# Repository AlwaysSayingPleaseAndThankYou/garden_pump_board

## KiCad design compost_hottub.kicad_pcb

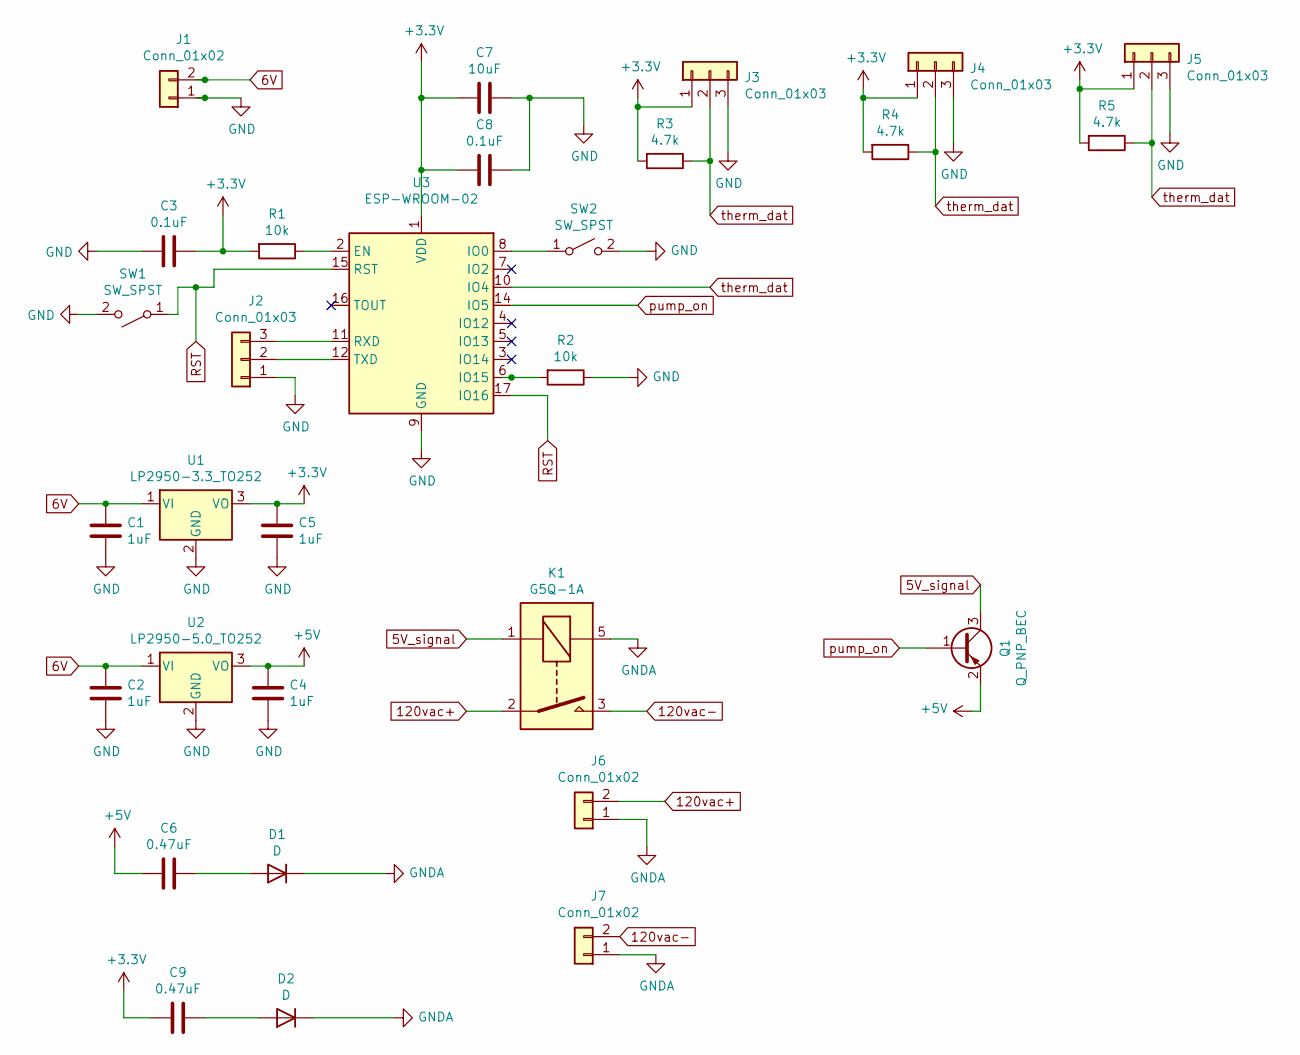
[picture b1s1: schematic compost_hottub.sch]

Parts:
C1, C2, C4, C5: 1uF; C_0201_0603Metric
C3, C8: 0.1uF; C_0201_0603Metric
C6, C9: 0.47uF; C_0201_0603Metric
C7: 10uF; C_0201_0603Metric
D1, D2: D; D_0201_0603Metric
J1: Conn_01x02; Hirose_DF13-02P-1.25DS_1x02_P1.25mm_Horizontal
J2, J3, J4, J5: Conn_01x03; FanPinHeader_1x03_P2.54mm_Vertical
J6: Conn_01x02; AMASS_XT30PW-F_1x02_P2.50mm_Horizontal
J7: Conn_01x02
K1: G5Q-1A; Relay_SPST_Omron-G5Q-1A
Q1: Q_PNP_BEC; TO-92
R1, R2: 10k; R_0402_1005Metric
R3, R4, R5: 4.7k; R_0402_1005Metric
SW1, SW2: SW_SPST; SW_DIP_SPSTx01_Slide_6.7x4.1mm_W8.61mm_P2.54mm_LowProfile
U1: LP2950-3.3_TO252; TO-252-2
U2: LP2950-5.0_TO252; TO-252-2
U3: ESP-WROOM-02

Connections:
5V_signal: K1.1, Q1.3 (C)
6V: C1.1, C2.1, J1.2, U1.1 (VI), U2.1 (VI)
120vac+: J6.2, K1.2
120vac-: J7.2, K1.3
+3V3: C3.1, C5.1, C7.2, C8.2, C9.2, J3.1, J4.1, J5.1, R1.2, R3.2, R4.2, R5.2, U1.3 (VO), U3.1 (VDD); also elsewhere on the board
+5V: C4.1, C6.2, Q1.2 (E), U2.3 (VO)
GND: C1.2, C2.2, C3.2, C4.2, C5.2, C7.1, C8.1, J1.1, J2.1, J3.3, J4.3, J5.3, R2.1, SW1.2 (B), SW2.2 (B), U1.2 (GND), U2.2 (GND), U3.9 (GND), U3.13 (GND), U3.18 (GND), U3.19 (GND); also elsewhere on the board
GNDA: D1.1 (K), D2.1 (K), J6.1, J7.1, K1.5; also elsewhere on the board
unnamed: C6.1, D1.2 (A)
unnamed: C9.1, D2.2 (A)
unnamed: J2.2, U3.12 (TXD)
unnamed: J2.3, U3.11 (RXD)
unnamed: R1.1, U3.2 (EN)
unnamed: R2.2, U3.6 (IO15)
unnamed: SW2.1 (A), U3.8 (IO0)
RST: SW1.1 (A), U3.15 (RST), U3.17 (IO16)
pump_on: Q1.1 (B), U3.14 (IO5)
therm_dat: J3.2, J4.2, J5.2, R3.1, R4.1, R5.1, U3.10 (IO4)

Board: 2 copper layers, 31 parts (0 on the bottom side), 17 nets, no tracks yet.

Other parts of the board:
C6#2: 0.47uF; C_0201_0603Metric
D1#2: D; D_0201_0603Metric

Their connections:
+3V3: C6#2.1, D1#2.2; also elsewhere on the board
GND: C6#2.2; also elsewhere on the board
GNDA: D1#2.1; also elsewhere on the board

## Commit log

2021-06-11 ignore me
2021-06-11 init
